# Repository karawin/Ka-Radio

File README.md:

# ** ESP8266 & VS1053 Wifi WebRadio ** #

### Ka-Radio, a WiFi shoutcast player based on ESP8266 and VS1053b chips</br>
See also the esp32 version at https://github.com/karawin/Ka-Radio32</br>

## Basic informations<BR/>
### New
A new android application is born
  
- KaRadio Remote Control by Vassilis Serasidis on google Play.

It is an easy and fast WiFi remote control for your KaRadio or KaRadio32 hardware.  
With this android app you can select the WebRadio station you want to play, set the volume and get the station information such as Station name, Genre, Bit rate, Meta data and more.   
Found it at
https://play.google.com/store/apps/details?id=com.serasidis.karadio.rc

Thanks Vassilis.  
###  
### Release 1.9 R8 - Built on 2021/01/01

#### Add On: add a lcd, a remote control, and other goodies: see https://github.com/karawin/Karadio-addons 

#### Attention:
The optional led is now on GPIO2. The blue led on the ESP8266 is blinking at the same rate.  
GPIO16 is now the Chip select for the external ram if any.<BR/>
The external ram is detected at boot time if present.    
To load this release, please flash   
boot_v1.6.bin at 0x0000,  
user1.4096.new.4.bin at 0x1000 ,  
user2.4096.new.4.bin at 0X81000,  
esp_init_data_default.bin at 0x3FC000   
and blank.bin at	0x3fe000   
After that, all next updates are done with the On The Air (OTA) feature.  
<BR/>  
See also https://hackaday.io/project/11570-wifi-webradio-with-esp8266-and-vs1053   

#### Loading the esp8266
The binaries are on ESP8266-Firmware/bin/upgrade/

#### First use
- If the access point of your router is not known, the webradio inits itself as an AP. Connect the wifi of your computer to the ssid "WifiWebRadio",  
- Browse to 192.168.4.1 to display the page, got to "setting" "Wifi" and configure your ssid ap, the password if any, the wanted IP or use dhcp if you know how to retrieve the dhcp given ip (terminal or scan of the network).
- In the gateway field, enter the ip address of your router.
- Validate. The equipment restart to the new configuration. Connect your wifi to your AP and browse to the ip given in configuration.
- Congratulation, you can edit your own station list. Dont forget to save your stations list in case of problem or for new equipments.
- if the AP is already know by the esp8266, the default ip is given by dhcp.
- a sample of stations list is on https://github.com/karawin/Ka-Radio/blob/master/ESP8266-Firmware/WebStations.txt . Can be uploaded via the web page.   
- Karadio can be controlled by the web interface or by the uart interface or by telnet. List of commands: type help  
- See the list of command at http://karadio.karawin.fr/Interface.txt  

### Generate Ka-Radio
see the http://karadio.karawin.fr/readme.txt file.

### History:
- Based on https://github.com/PiotrSperka/ESP8266-WebRadio<br />
- New development based on the new https://github.com/espressif/ESP8266_RTOS_SDK<br />
- Compiled with [esp-open-sdk](https://github.com/pfalcon/esp-open-sdk)<br />
- Compatible with mobile<br />
- Stable<br />
- tools to save and restore the stations database<br /><br />
- prototype made with:<br />
-- http://fr.aliexpress.com/item/MB102-Breadboard-Power-Supply-Module-3-3V-5V-For-Solderless-Breadboard/2027279953.html (0.74 euros)<br />
-- http://www.ebay.fr/itm/121775761053?_trksid=p2057872.m2749.l2649&ssPageName=STRK%3AMEBIDX%3AIT  (3,09 euros)<br />
-- http://www.ebay.fr/itm/401046111343?_trksid=p2060353.m2749.l2649&ssPageName=STRK%3AMEBIDX%3AIT  (6 euros)<br />
-- http://www.ebay.fr/itm/131683794035?_trksid=p2060353.m2749.l2649&ssPageName=STRK%3AMEBIDX%3AIT  (1.05 euros)<br />
-- http://fr.aliexpress.com/item/USB-to-TTL-converter-UART-module-CH340G-CH340-3-3V-5V-switch/32392228218.html?detailNewVersion=2 (0.59 euro)<br />
-- some wires ...<br /><br />
- Wiring: <br />
From ESP8266_ESP12( 3.3 v) to VS1053 (5 v)<br />
REST<br />
ADC   if control panel is not used, this input must be grounded.<br />
CH_PD to 3.3v<br />
GPIO16 (a 1Hz output)<br />
GPIO14 to VS1053 SCK<br />
GPIO12 to VS1053 MISO<br />
GPIO13 to VS1053 MOSI<br />
<br />
TXD to   CH340G UART rx<br />
RXD from CH340G UART tx<br />
GPIO05 to VS1053 XDCS<br />
GPIO04 to VS1053 DREQ<br />
GPIO00 to VS1053 XRST<br />
GPIO02<br />
GPIO15 to VS1053 XCS<br />
<br/>
Optional external ram (23LCV1024) support (1:CS/=GPIO16 2:MISO=GPIO12 3:NC 4:GND 5:MOSI=GPIO13 6:SCK=GPIO14 7:GND 8:3.3v)<br/>
If your chip has a /Vhold in place of /VBAT, the pin 7 must be wired to VCC (pin8)<br/>
Attention:<br>
	The optional led is now on GPIO2. The blue led on the ESP8266 is blinking at the same rate.<br/>
	GPIO16 is now the Chip select for the external ram if any.<br/>
	The external ram is detected at boot time if present.<br/>

## Used hardware
WiFi : ESP8266 (ESP-12 with 32Mbits flash)<br />
Additional MCU (as a bridge UART<=>UI): AVR<br />
Audio decoder: VS1053<br />

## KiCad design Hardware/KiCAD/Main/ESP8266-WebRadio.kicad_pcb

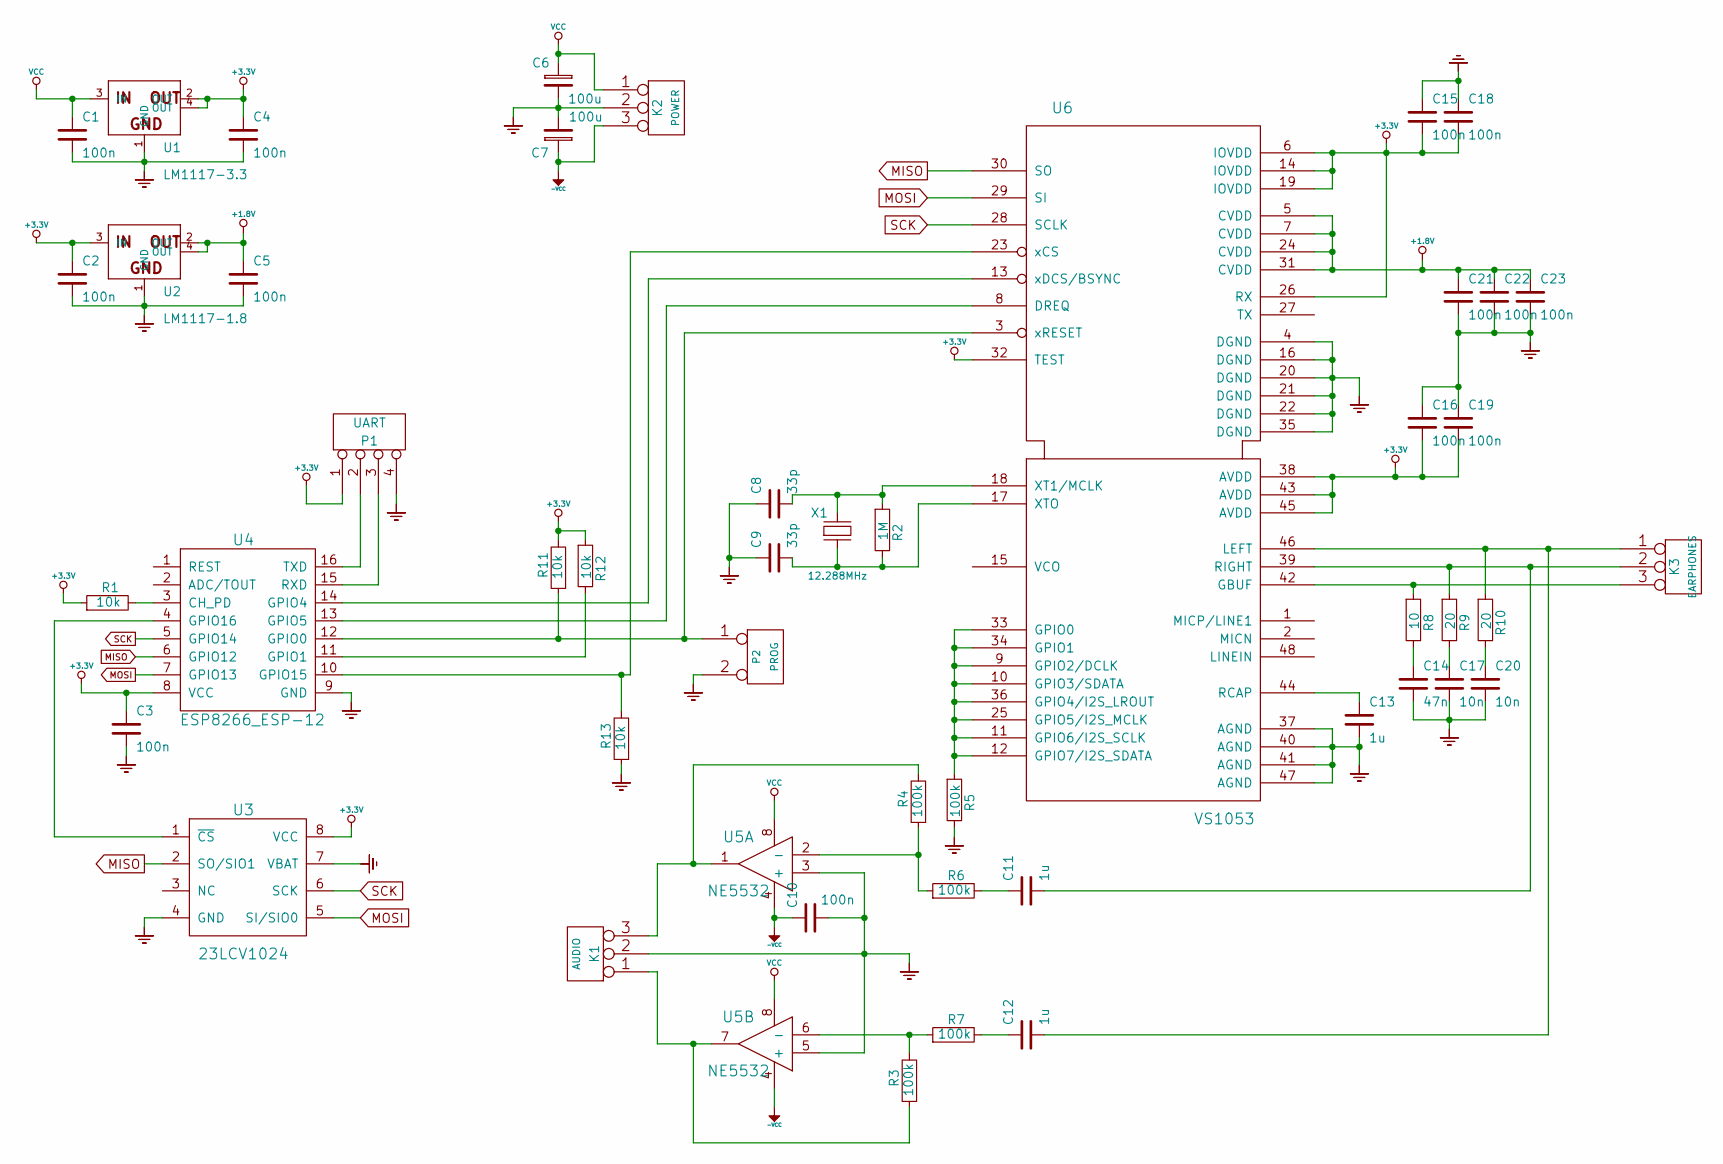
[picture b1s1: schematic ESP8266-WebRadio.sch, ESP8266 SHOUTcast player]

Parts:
C1, C2, C3, C4, C5, C10, C15, C16, C18, C19, C21, C22, C23: 100n
C6, C7: 100u
C8, C9: 33p
C11, C12, C13: 1u
C14: 47n
C17, C20: 10n
K1: AUDIO
K2: POWER
K3: EARPHONES
P1: UART
P2: PROG
R1, R11, R12, R13: 10k
R2: 1M
R3, R4, R5, R6, R7: 100k
R8: 10
R9, R10: 20
U1: LM1117-3.3
U2: LM1117-1.8
U3: 23LCV1024
U4: ESP8266_ESP-12
U5: NE5532
U6: VS1053
X1: 12.288MHz

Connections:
+1.8V: C5.1, C21.1, C22.1, C23.1, U2.2 (OUT), U2.4 (OUT), U6.5 (CVDD), U6.7 (CVDD), U6.24 (CVDD), U6.31 (CVDD)
+3.3V: C2.1, C3.1, C4.1, C15.2, C16.2, C18.2, C19.2, P1.1, R1.1, R11.2, R12.1, U1.2 (OUT), U1.4 (OUT), U2.3 (IN), U3.8 (VCC), U4.8 (VCC), U6.6 (IOVDD), U6.14 (IOVDD), U6.19 (IOVDD), U6.26 (RX), U6.32 (TEST), U6.38 (AVDD), U6.43 (AVDD), U6.45 (AVDD)
-6V: C7.1, C10.1, K2.3, U5.4
GND: C1.2, C2.2, C3.2, C4.2, C5.2, C6.2, C7.2, C8.1, C9.1, C10.2, C13.2, C14.2, C15.1, C16.1, C17.2, C18.1, C19.1, C20.2, C21.2, C22.2, C23.2, K1.2 (PM), K2.2 (PM), P1.4, P2.2 (PM), R5.2, R13.1, U1.1 (GND), U2.1 (GND), U3.4 (GND), U3.7 (VBAT), U4.9 (GND), U5.3 (+), U5.5 (+), U6.4 (DGND), U6.16 (DGND), U6.20 (DGND), U6.21 (DGND), U6.22 (DGND), U6.35 (DGND), U6.37 (AGND), U6.40 (AGND), U6.41 (AGND), U6.47 (AGND); also elsewhere on the board
MISO: U3.2 (SO/SIO1), U4.6 (GPIO12), U6.30 (SO)
MOSI: U3.5 (SI/SIO0), U4.7 (GPIO13), U6.29 (SI)
unnamed: C8.2, R2.1, U6.18 (XT1/MCLK), X1.2
unnamed: C9.2, R2.2, U6.17 (XTO), X1.1
unnamed: R5.1, U6.9 (GPIO2/DCLK), U6.10 (GPIO3/SDATA), U6.11 (GPIO6/I2S_SCLK), U6.12 (GPIO7/I2S_SDATA), U6.25 (GPIO5/I2S_MCLK), U6.33 (GPIO0), U6.34 (GPIO1), U6.36 (GPIO4/I2S_LROUT)
unnamed: C13.1, U6.44 (RCAP)
unnamed: C12.1, R7.2
unnamed: C11.1, R6.2
unnamed: R4.1, R6.1, U5.2 (-)
unnamed: R3.2, R7.1, U5.6 (-)
unnamed: K1.1, R3.1, U5.7
unnamed: K1.3, R4.2, U5.1
unnamed: R12.2, U4.11 (GPIO1)
unnamed: P1.2, U4.16 (TXD)
unnamed: P1.3, U4.15 (RXD)
unnamed: C17.1, R9.2
unnamed: K3.3, R8.1, U6.42 (GBUF)
unnamed: C11.2, K3.2 (PM), R9.1, U6.39 (RIGHT)
unnamed: C12.2, K3.1, R10.1, U6.46 (LEFT)
unnamed: C14.1, R8.2
unnamed: C20.1, R10.2
unnamed: U3.1 (~CS), U4.4 (GPIO16)
unnamed: P2.1, R11.1, U4.12 (GPIO0), U6.3 (xRESET)
unnamed: R1.2, U4.3 (CH_PD)
unnamed: R13.2, U4.10 (GPIO15), U6.23 (xCS)
unnamed: U4.14 (GPIO4), U6.13 (xDCS/BSYNC)
unnamed: U4.13 (GPIO5), U6.8 (DREQ)
SCK: U3.6 (SCK), U4.5 (GPIO14), U6.28 (SCLK)
VCC: C1.1, C6.1, K2.1, U1.3 (IN), U5.8

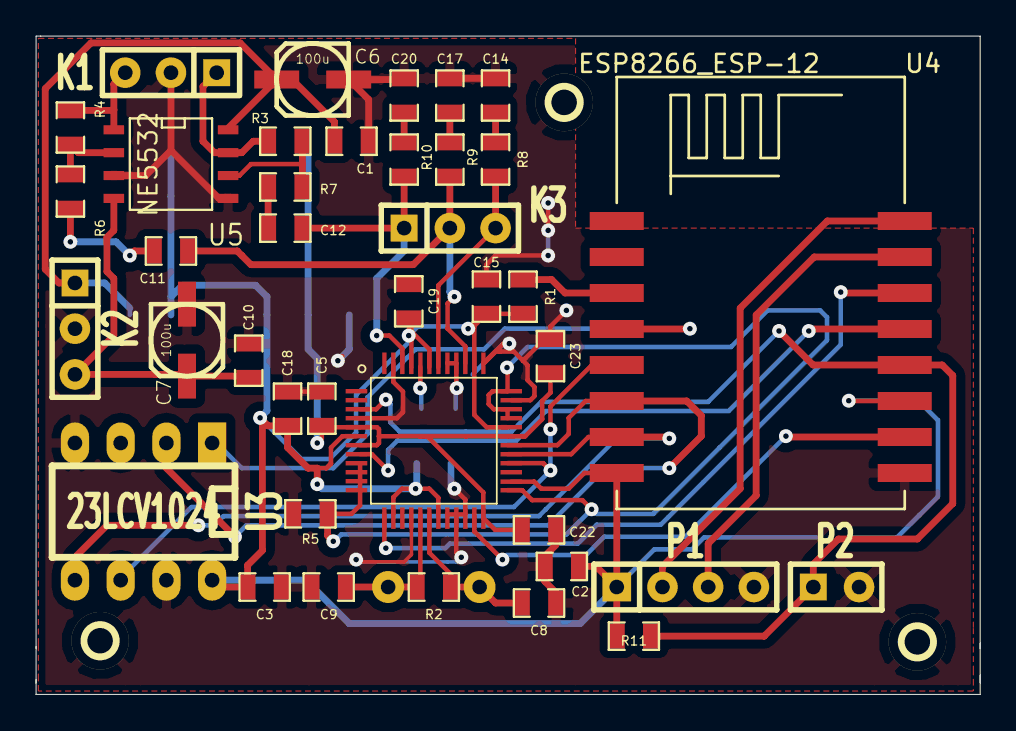
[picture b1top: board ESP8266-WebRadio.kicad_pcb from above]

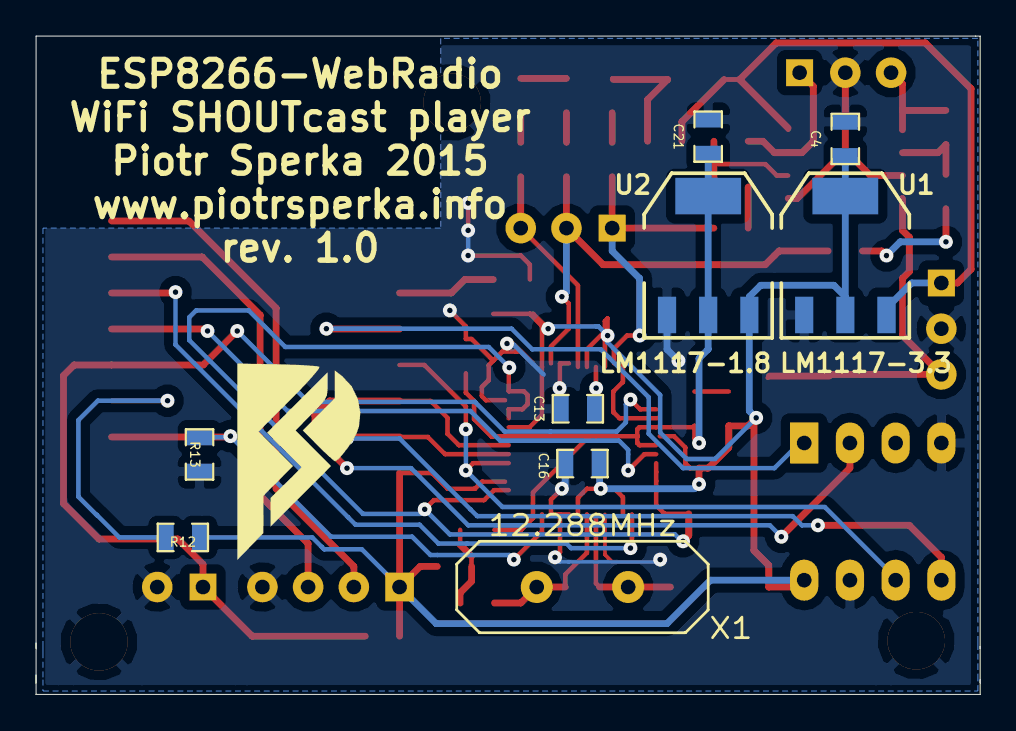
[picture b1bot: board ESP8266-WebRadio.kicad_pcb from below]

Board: 2 copper layers, 52.5 x 36.6 mm, 51 parts (9 on the bottom side), 33 nets.

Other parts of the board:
1PIN, 1PIN#2: P***; 1pin
VAL: REF; Logo

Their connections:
GND: 1PIN.1, 1PIN#2.1; also elsewhere on the board

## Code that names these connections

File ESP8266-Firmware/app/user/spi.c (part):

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		PIN_FUNC_SELECT(PERIPHS_IO_MUX_SD_DATA1_U, 1);	
	}else if(spi_no==HSPI){
		WRITE_PERI_REG(PERIPHS_IO_MUX, 0x105|(clock_div_flag<<9)); //Set bit 9 if 80MHz sysclock required
		PIN_FUNC_SELECT(PERIPHS_IO_MUX_MTDI_U, 2); //GPIO12 is HSPI MISO pin (Master Data In)
		PIN_FUNC_SELECT(PERIPHS_IO_MUX_MTCK_U, 2); //GPIO13 is HSPI MOSI pin (Master Data Out)
		PIN_FUNC_SELECT(PERIPHS_IO_MUX_MTMS_U, 2); //GPIO14 is HSPI CLK pin (Clock)
		//PIN_FUNC_SELECT(PERIPHS_IO_MUX_MTDO_U, 2); //GPIO15 is HSPI CS pin (Chip Select / Slave Select)
	}

}
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
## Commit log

2016-06-15 New repository
2016-06-16 Correction for NodeMcu with adc dividor and grounded adc.
2016-06-16 New start
2016-06-16 removed some traces
2016-06-18 piotSperka merged this release.
2016-06-26 Release 1.0.5
2016-06-27 Increase stack size a bit...
2016-06-27 Readme
2016-07-19 Release 1.0.6
2016-07-21 External ram detection
    External ram detection
    and Save stations from webradio changed for edge
2016-07-21 History in upgrade
2016-07-29 Increase spi clock for external ram
2016-07-29 Increas spi clock for external ram
    restore spi speed before flash read/write
2016-08-01 receive buffer too big
2016-08-14 Release 1.0.7
2016-09-12 Release 1.0.8
2016-09-12 Release 1.0.8. Readme
2016-09-14 A little bug in metadata
2016-09-15 cleanup
2016-09-16 IF a station is not found, indicate it to the interface in the name.
2016-09-17 A little crash removed...
2016-09-29 Release 1.0.9
2016-09-29 Release 1.0.9 Md file
2016-10-01 I2S mistake corrected
2016-10-10 Release 1.0.10
2016-10-10 1.0.10 Led blink too quickly for my taste.
2016-10-16 release 1.1.0
2016-10-16 Readme 1.1.0
2016-10-29 Release 1.1.1
2016-10-29 Release 1.1.1 ReadMe
2016-11-09 karadioU8glib.zip added: lcd software
    karadioU8glib.zip is an arduino sketch to build a lcd display for
    karadio.
    Some many other little improvments in karadion.
    No new features added.
2016-11-23 1.1.2
2016-11-26 1.1.2 stable
2016-11-26 controle.pdf updated
2016-12-01 Release 1.1.3
2016-12-03 lcd & remote arduino software
2017-01-02 Cleanup 1.1.3
2017-01-08 pre 1.1.4
2017-01-09 1.1.4
2017-01-09 ReadMe 1.1.4
2017-01-10 1.1.4 links in readme
2017-01-14 1.1.5
2017-01-14 1.1.5 readme.md
2017-01-20 mistake default ip
2017-01-24 lcd update
2017-01-25 1.1.5, AP mode corrected
2017-01-31 Wire external ram
2017-02-02 Release 1.1.6
2017-02-02 1.1.6 Read.me
2017-02-09 1.1.7
2017-02-09 Readme 1.1.7
2017-02-10 1.1.7+
    volume offset correction
2017-02-12 Fixed the bug with reduced size of payload buffer. TCP package data size checked with tcpdump. It is 1024 bytes now. Faster loading of webpage.
2017-02-12 servfile update
2017-03-30 Fix syntax errors.
2017-03-30 Fix syntax errors (test)
2017-04-04 Release 1.1.8
2017-04-04 1.1.8 correction
2017-04-04 Readme 1.1.8
2017-04-13 Release 1.2
2017-04-13 Readme 1.2
2017-04-14 Priority uart
2017-04-18 README.md formatting changes
2017-04-20 restore index.html
2017-05-02 Added some missing include and cleaned the Makefile
2017-05-02 Update readme for yui_compressor
2017-05-07 added the readme.txt
2017-05-07 Added readme.txt to generate Ka-Radio
2017-05-08 KaRadio-install.sh added
2017-05-16 Minor details for the volume
2017-05-22 Release 1.2.2
2017-05-30 Release 1.3
2017-06-01 Readme update
2017-06-06 Rlease 1.3.1
2017-06-19 Release 1.3.2
2017-06-19 1.3.2
2017-06-30 Release 1.3.3
    Bugs removed
2017-07-01 interface.txt update
2017-07-04 Control panel on bar ESP
2017-07-11 1.3.4
2017-07-19 Release 1.4
    July, 19 2017
2017-07-19 patch comment inverted.
2017-07-24 Release 1.5
    New KaraDio based on Espressif RTOS SDK 1.5.0-dev
2017-07-25 1.5 update
2017-07-29 1.4.1 released
    Back to 1.4 line
2017-07-30 Cleaning things
2017-07-31 Revision 4
2017-07-31 Some labels changed.
2017-08-01 1.4.2
2017-08-01 1.4.2 R3
2017-08-07 Release 1.5
2017-08-08 1.5 R3
2017-08-11 1.5.1 R1
2017-08-12 offset volume negative was wrong
2017-08-25 R 1.6
2017-08-25 R 1.6 json correction
2017-08-27 Ajust uart speed not working. Corrected.
2017-09-05 little change on uart
2017-09-17 Release 1.6.1
2017-10-21 eeprom
2017-11-02 release 1.6.2
2017-11-02 Readme 1.6.2
2017-11-08 1.6.2 R2
2017-11-08 1.6.2 R3
2017-11-22 ntp server changed
2017-11-22 Version 1.6.2 R4
2017-12-27 1.6.3: Correction for stations with the char & in path.
2018-09-05 pre release 1.7
    Web command prev and next added
    mdns in progress.
2018-09-09 pre 1.7 mdns
2018-09-09 Version 1.7 official
    <ul>
    <li>mDns added </li>
    <li>web commands next and prev added</li>
    <li>uart or teknet command sys.host added.</li>
    </ul>
2018-09-09 a wrong label
2018-11-21 Replacing yui compressor with python script
2018-11-27 1.7 R1
    Title on top of the page
2019-01-15 style and readme.md
2019-02-01 Release 1.8 R0
2019-02-01 1.8 volume arrow
2019-02-01 Correction for instant-play
2019-02-06 Release 1.8 R1
2019-02-07 script.js detail
2019-02-11 1.8 R2
2019-02-11 Corrected: Wifi infos, upgrade
2019-02-15 prerelease 1.9 R0
2019-02-21 ESP8266 RTOS SDK 2.0.0
2019-02-25 inteface
2019-02-25 Revert "ESP8266 RTOS SDK 2.0.0"
2019-02-25 Restore ESP8266 RTOS SDK 2.0.0
2019-02-26 Release 1.9 R0 RTOS_SDK 2.0.0
2019-02-27 1.9 R0 final
2019-02-27 1.9 R0 binaries
2019-02-27 README.md
2019-02-28 Disable telnet in AP mode
2019-03-02 Html infos bug
2019-03-07 keyboard on web (ctrl space)
2019-04-08 Release 1.9 R1
2019-04-15 1.9 R2
    AP mode was not working
2019-04-28 Release 1.9 R3
2019-05-18 lwip update. AP corretion if no ip given.
2019-05-26 1.9 R4
    lwip tuning
2019-06-30 Release 1.9 R5
    json correction
2019-08-01 Problem on AP mode due to the lwip layer. Resolved
    Seems resolved
2020-01-11 Release 1.9 R6
2020-12-20 Release 1.9 R7
    new vs1053b patch 2.9
2021-01-01 Release 1.9 R8
    VS1053B Code cleaned
2021-01-09 Release 9
    VS1053b detection improved.
    On some old vs1003/vs1053 boards, loading the vs1053 patch result in no
    sound because the vs1053 board resetted to the midi mode. Corrected now.
    Setting panel correction.
2021-01-09 Bug no patch
2021-01-10 WebStations.txt update
2021-01-28 Release V2.0R0
    Better handling of long header moved playlist
    timezone suggestion
    Better monitoring
2021-02-10 Release V2.1 R0
    No clear password in message for security.
2021-02-14 Release V2.1 R0 new
    <ul id="ordered">
    <li>Security: the ssid passwords are no longer sent
    on each "Setting" display, but only when changed.</li>
    <li>Bug fixed:
    in parse playlist. Possible memory leak. Thanks to HmarikBel</li>
    <li>Bug fixed: Special char in station name was incorrectly sent.</li>
2021-02-15 2.1 R0 Little pb
    New station not saved.
2021-03-12 Release 2.1 R1
    Some mistakes on wifi init
2021-03-12 2.1 R1 forgot one file
2021-03-24 Readme.md update
2022-10-22 Fix for wifi password 2 not saved correctly

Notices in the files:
ESP8266-Firmware/app/user/spi.c:
The MIT License (MIT)
Copyright (c) 2015 David Ogilvy (MetalPhreak)
